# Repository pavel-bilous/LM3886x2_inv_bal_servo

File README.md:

# LM3886x2_inv_bal_servo

## Schematics:

Two paralleled LM3886 are used to double the current drive and to increase the power output. Safe voltage to power the amplifier is 36V.
Gain is set to 11 V/V. Benefits of using two chips in parallel include: increase of the output drive capability of an amplifier, reduced voltage noise (better SNR), and reduced output offset error.

## PCB rendered in 3d:

## PCB layout:

Bottom layer is GND. Top layer is signal + power and GND poured in between. Stiching vias are then applied to connect bottom and top GND planes to ensure those are as close to 0 as possible.

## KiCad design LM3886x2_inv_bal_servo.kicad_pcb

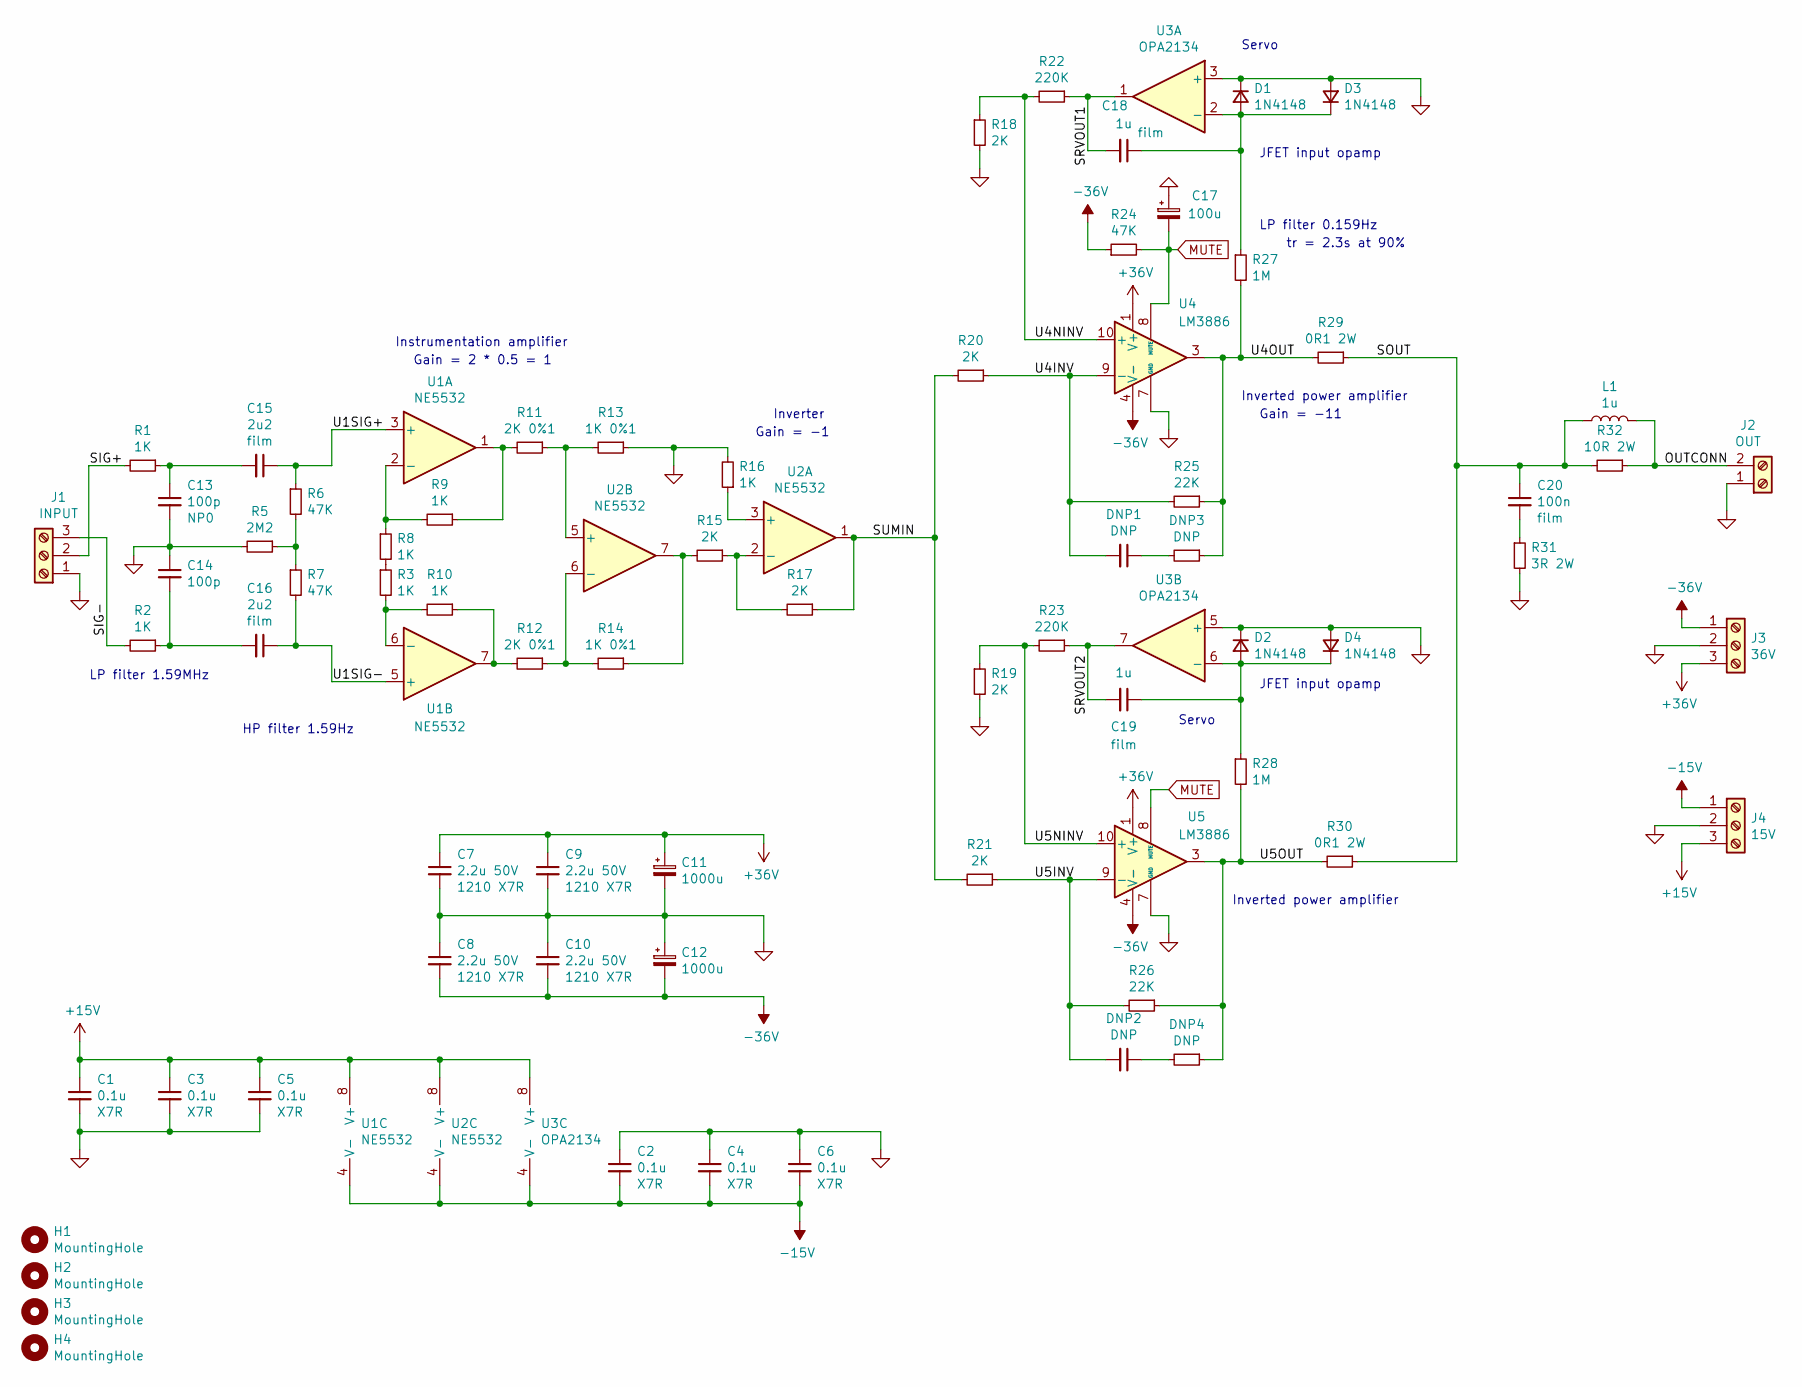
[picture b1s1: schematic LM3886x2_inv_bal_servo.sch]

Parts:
C1, C2, C3, C4, C5, C6: 0.1u; C_1206_3216Metric_Pad1.42x1.75mm_HandSolder
C7, C8, C9, C10: 2.2u 50V; C_1210_3225Metric_Pad1.42x2.65mm_HandSolder
C11, C12: 1000u; CP_Radial_D16.0mm_P7.50mm
C13, C14: 100p; C_1206_3216Metric_Pad1.42x1.75mm_HandSolder
C15, C16: 2u2; C_Rect_L7.2mm_W5.5mm_P5.00mm_FKS2_FKP2_MKS2_MKP2
C17: 100u; CP_Radial_D8.0mm_P3.80mm
C18, C19: 1u; C_Rect_L7.2mm_W5.5mm_P5.00mm_FKS2_FKP2_MKS2_MKP2
C20: 100n; C_Rect_L7.2mm_W2.5mm_P5.00mm_FKS2_FKP2_MKS2_MKP2
D1, D2, D3, D4: 1N4148; D_SOD-123
DNP1, DNP2: DNP; C_0805_2012Metric_Pad1.15x1.40mm_HandSolder
DNP3, DNP4: DNP; R_1206_3216Metric_Pad1.42x1.75mm_HandSolder
H1, H2, H3, H4: MountingHole; MountingHole_3.2mm_M3_Pad_Via
J1: INPUT; TerminalBlock_ Amphenol_01_03_P3.50mm
J2: OUT; TerminalBlock_CUI_01x02_P5.00mm
J3: 36V; TerminalBlock_CUI_01x03_P5.00mm
J4: 15V; TerminalBlock_ Amphenol_01_03_P3.50mm
L1: 1u; Inductor_DIY
R1, R2, R3, R8, R9, R10, R16: 1K; R_1206_3216Metric_Pad1.42x1.75mm_HandSolder
R5: 2M2; R_1206_3216Metric_Pad1.42x1.75mm_HandSolder
R6, R7, R24: 47K; R_1206_3216Metric_Pad1.42x1.75mm_HandSolder
R11, R12: 2K 0%1; R_1206_3216Metric_Pad1.42x1.75mm_HandSolder
R13, R14: 1K 0%1; R_1206_3216Metric_Pad1.42x1.75mm_HandSolder
R15, R17, R18, R19, R20, R21: 2K; R_1206_3216Metric_Pad1.42x1.75mm_HandSolder
R22, R23: 220K; R_1206_3216Metric_Pad1.42x1.75mm_HandSolder
R25, R26: 22K; R_1206_3216Metric_Pad1.42x1.75mm_HandSolder
R27, R28: 1M; R_1206_3216Metric_Pad1.42x1.75mm_HandSolder
R29, R30: 0R1 2W; R_2512_6332Metric_Pad1.52x3.35mm_HandSolder
R31: 3R 2W; R_2512_6332Metric_Pad1.52x3.35mm_HandSolder
R32: 10R 2W; R_2512_6332Metric_Pad1.52x3.35mm_HandSolder
U1, U2: NE5532; SOIC-8_3.9x4.9mm_P1.27mm
U3: OPA2134; SOIC-8_3.9x4.9mm_P1.27mm
U4, U5: LM3886; TO-220-11_P3.4x5.08mm_StaggerOdd_Lead4.85mm_Vertical

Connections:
+15V: C1.1, C3.1, C5.1, J4.3, U1.8 (V+), U2.8 (V+), U3.8 (V+)
+36V: C7.1, C9.1, C11.1, J3.3, U4.1 (V+), U4.5 (V+), U5.1 (V+), U5.5 (V+)
-15V: C2.2, C4.2, C6.2, J4.1, U1.4 (V-), U2.4 (V-), U3.4 (V-)
-36V: C8.2, C10.2, C12.2, J3.1, R24.1, U4.4 (V-), U5.4 (V-)
/OUTCONN: J2.2, L1.2, R32.1
/SIG+: J1.2, R1.2
/SIG-: J1.3, R2.2
/SOUT: C20.1, L1.1, R29.1, R30.1, R32.2
/SRVOUT1: C18.2, R22.1, U3.1
/SRVOUT2: C19.2, R23.1, U3.7
/SUMIN: R17.1, R20.2, R21.2, U2.1
/U1SIG+: C15.1, R6.1, U1.3 (+)
/U1SIG-: C16.1, R7.2, U1.5 (+)
/U4INV: DNP1.2, R20.1, R25.2, U4.9 (-)
/U4NINV: R18.1, R22.2, U4.10 (+)
/U4OUT: DNP3.1, R25.1, R27.2, R29.2, U4.3
/U5INV: DNP2.2, R21.1, R26.2, U5.9 (-)
/U5NINV: R19.1, R23.2, U5.10 (+)
/U5OUT: DNP4.1, R26.1, R28.2, R30.2, U5.3
GND: C1.2, C2.1, C3.2, C4.1, C5.2, C6.1, C7.2, C8.1, C9.2, C10.1, C11.2, C12.1, C13.2, C14.1, C17.1, D1.1 (K), D2.1 (K), D3.2 (A), D4.2 (A), J1.1, J2.1, J3.2, J4.2, R5.2, R13.1, R16.2, R18.2, R19.2, R31.2, U3.3 (+), U3.5 (+), U4.7 (GND), U5.7 (GND)
MUTE: C17.2, R24.2, U4.8 (MUTE), U5.8 (MUTE)
unnamed: C13.1, C15.2, R1.1
unnamed: C14.2, C16.2, R2.1
unnamed: C18.1, D1.2 (A), D3.1 (K), R27.1, U3.2 (-)
unnamed: C19.1, D2.2 (A), D4.1 (K), R28.1, U3.6 (-)
unnamed: C20.2, R31.1
unnamed: DNP1.1, DNP3.2
unnamed: DNP2.1, DNP4.2
unnamed: R3.1, R8.2
unnamed: R5.1, R6.2, R7.1
unnamed: R8.1, R9.2, U1.2 (-)
unnamed: R10.1, R12.2, U1.7
unnamed: R3.2, R10.2, U1.6 (-)
unnamed: R11.1, R13.2, U2.5 (+)
unnamed: R9.1, R11.2, U1.1
unnamed: R12.1, R14.2, U2.6 (-)
unnamed: R14.1, R15.2, U2.7
unnamed: R15.1, R17.2, U2.2 (-)
unnamed: R16.1, U2.3 (+)

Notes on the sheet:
Instrumentation amplifier
Inverter
Servo
Inverted power amplifier
LP filter 1.59MHz
HP filter 1.59Hz
LP filter 0.159Hz
tr = 2.3s at 90%
Gain = -11
Gain = -1
Gain = 2 * 0.5 = 1
JFET input opamp

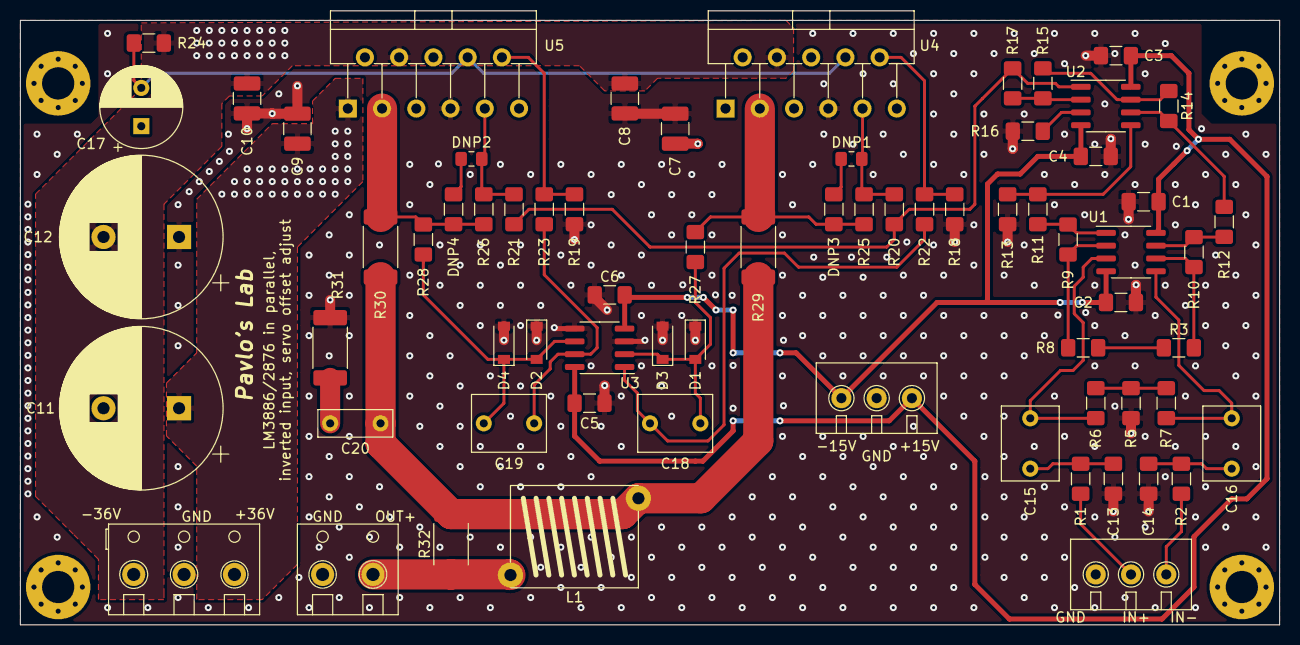
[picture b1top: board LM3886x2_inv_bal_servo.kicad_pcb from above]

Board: 2 copper layers, 125.0 x 60.0 mm, 73 parts (0 on the bottom side), 39 nets.

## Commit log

2023-06-29 updated sch
2023-07-01 pcb is started
2023-07-03 finished PCB layout
2023-07-03 added sch
